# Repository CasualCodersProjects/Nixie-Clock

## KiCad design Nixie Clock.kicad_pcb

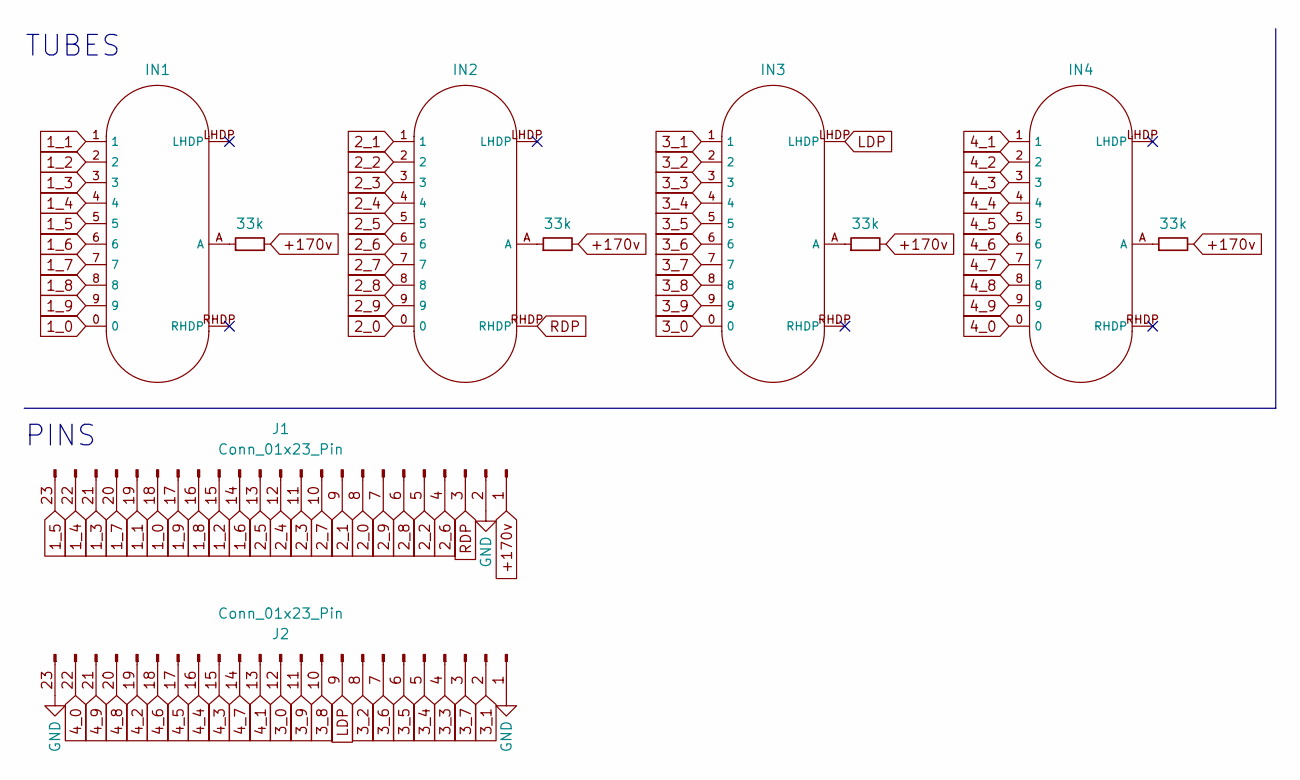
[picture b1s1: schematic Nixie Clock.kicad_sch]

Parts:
IN1, IN2, IN3, IN4: IN-16
J1, J2: Conn_01x23_Pin; PinHeader_1x23_P2.54mm_Vertical_SMD_Pin1Left
R1, R2, R3, R4: 33k; R_0805_2012Metric

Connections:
1_0: IN1.0, J1.18
1_1: IN1.1, J1.19
1_2: IN1.2, J1.15
1_3: IN1.3, J1.21
1_4: IN1.4, J1.22
1_5: IN1.5, J1.23
1_6: IN1.6, J1.14
1_7: IN1.7, J1.20
1_8: IN1.8, J1.16
1_9: IN1.9, J1.17
2_0: IN2.0, J1.8
2_1: IN2.1, J1.9
2_2: IN2.2, J1.5
2_3: IN2.3, J1.11
2_4: IN2.4, J1.12
2_5: IN2.5, J1.13
2_6: IN2.6, J1.4
2_7: IN2.7, J1.10
2_8: IN2.8, J1.6
2_9: IN2.9, J1.7
3_0: IN3.0, J2.12
3_1: IN3.1, J2.2
3_2: IN3.2, J2.8
3_3: IN3.3, J2.4
3_4: IN3.4, J2.5
3_5: IN3.5, J2.6
3_6: IN3.6, J2.7
3_7: IN3.7, J2.3
3_8: IN3.8, J2.10
3_9: IN3.9, J2.11
4_0: IN4.0, J2.22
4_1: IN4.1, J2.13
4_2: IN4.2, J2.19
4_3: IN4.3, J2.15
4_4: IN4.4, J2.16
4_5: IN4.5, J2.17
4_6: IN4.6, J2.18
4_7: IN4.7, J2.14
4_8: IN4.8, J2.20
4_9: IN4.9, J2.21
+170v: J1.1, R1.2, R2.2, R3.2, R4.2
GND: J1.2, J2.1, J2.23
LDP: IN3.LHDP, J2.9
unnamed: IN1.A, R1.1
unnamed: IN2.A, R2.1
unnamed: IN3.A, R3.1
unnamed: IN4.A, R4.1
RDP: IN2.RHDP, J1.3

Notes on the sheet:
TUBES
PINS

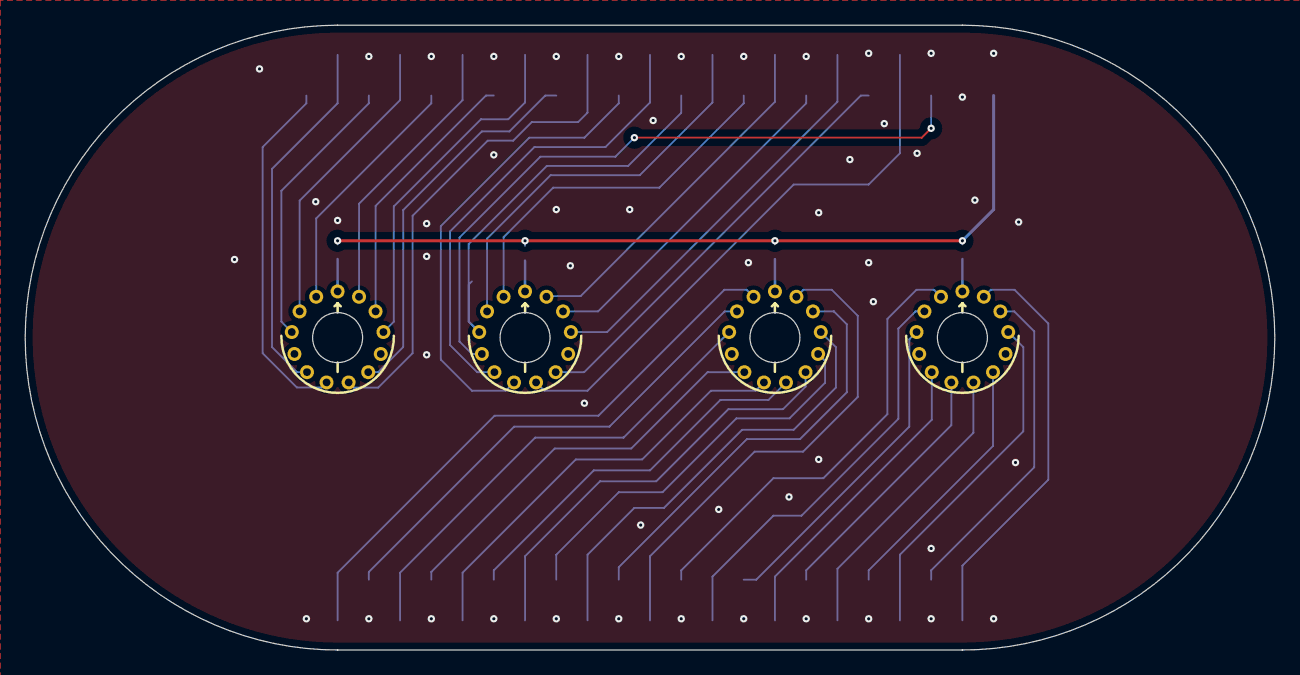
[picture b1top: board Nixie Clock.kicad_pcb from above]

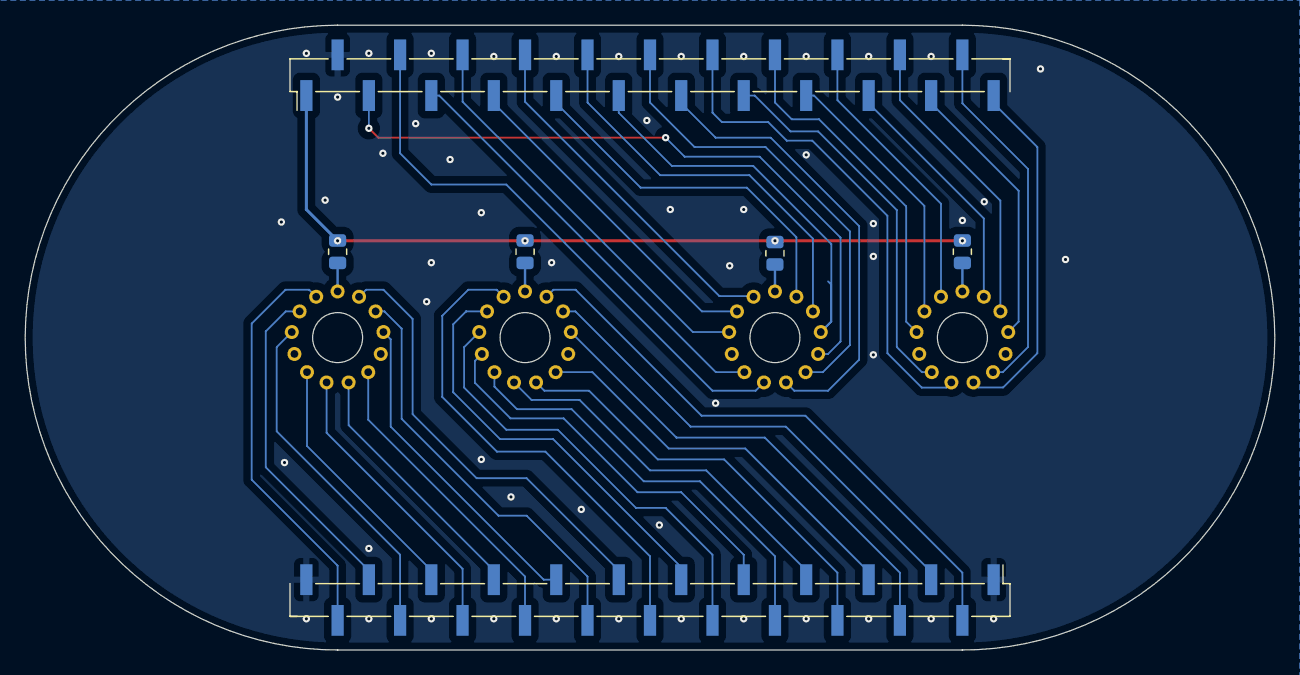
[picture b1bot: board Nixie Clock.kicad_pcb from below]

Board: 2 copper layers, 101.6 x 50.8 mm, 10 parts (6 on the bottom side), 48 nets.

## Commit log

2023-07-02 Created top plate ideas
2023-07-02 Finished top plate
2023-07-05 Finalized Top Plate with Gerbers
2023-07-05 Finalized Bottom Plate with Gerbers
2023-07-21 Added Clock Code
2024-02-09 Add fastLED
